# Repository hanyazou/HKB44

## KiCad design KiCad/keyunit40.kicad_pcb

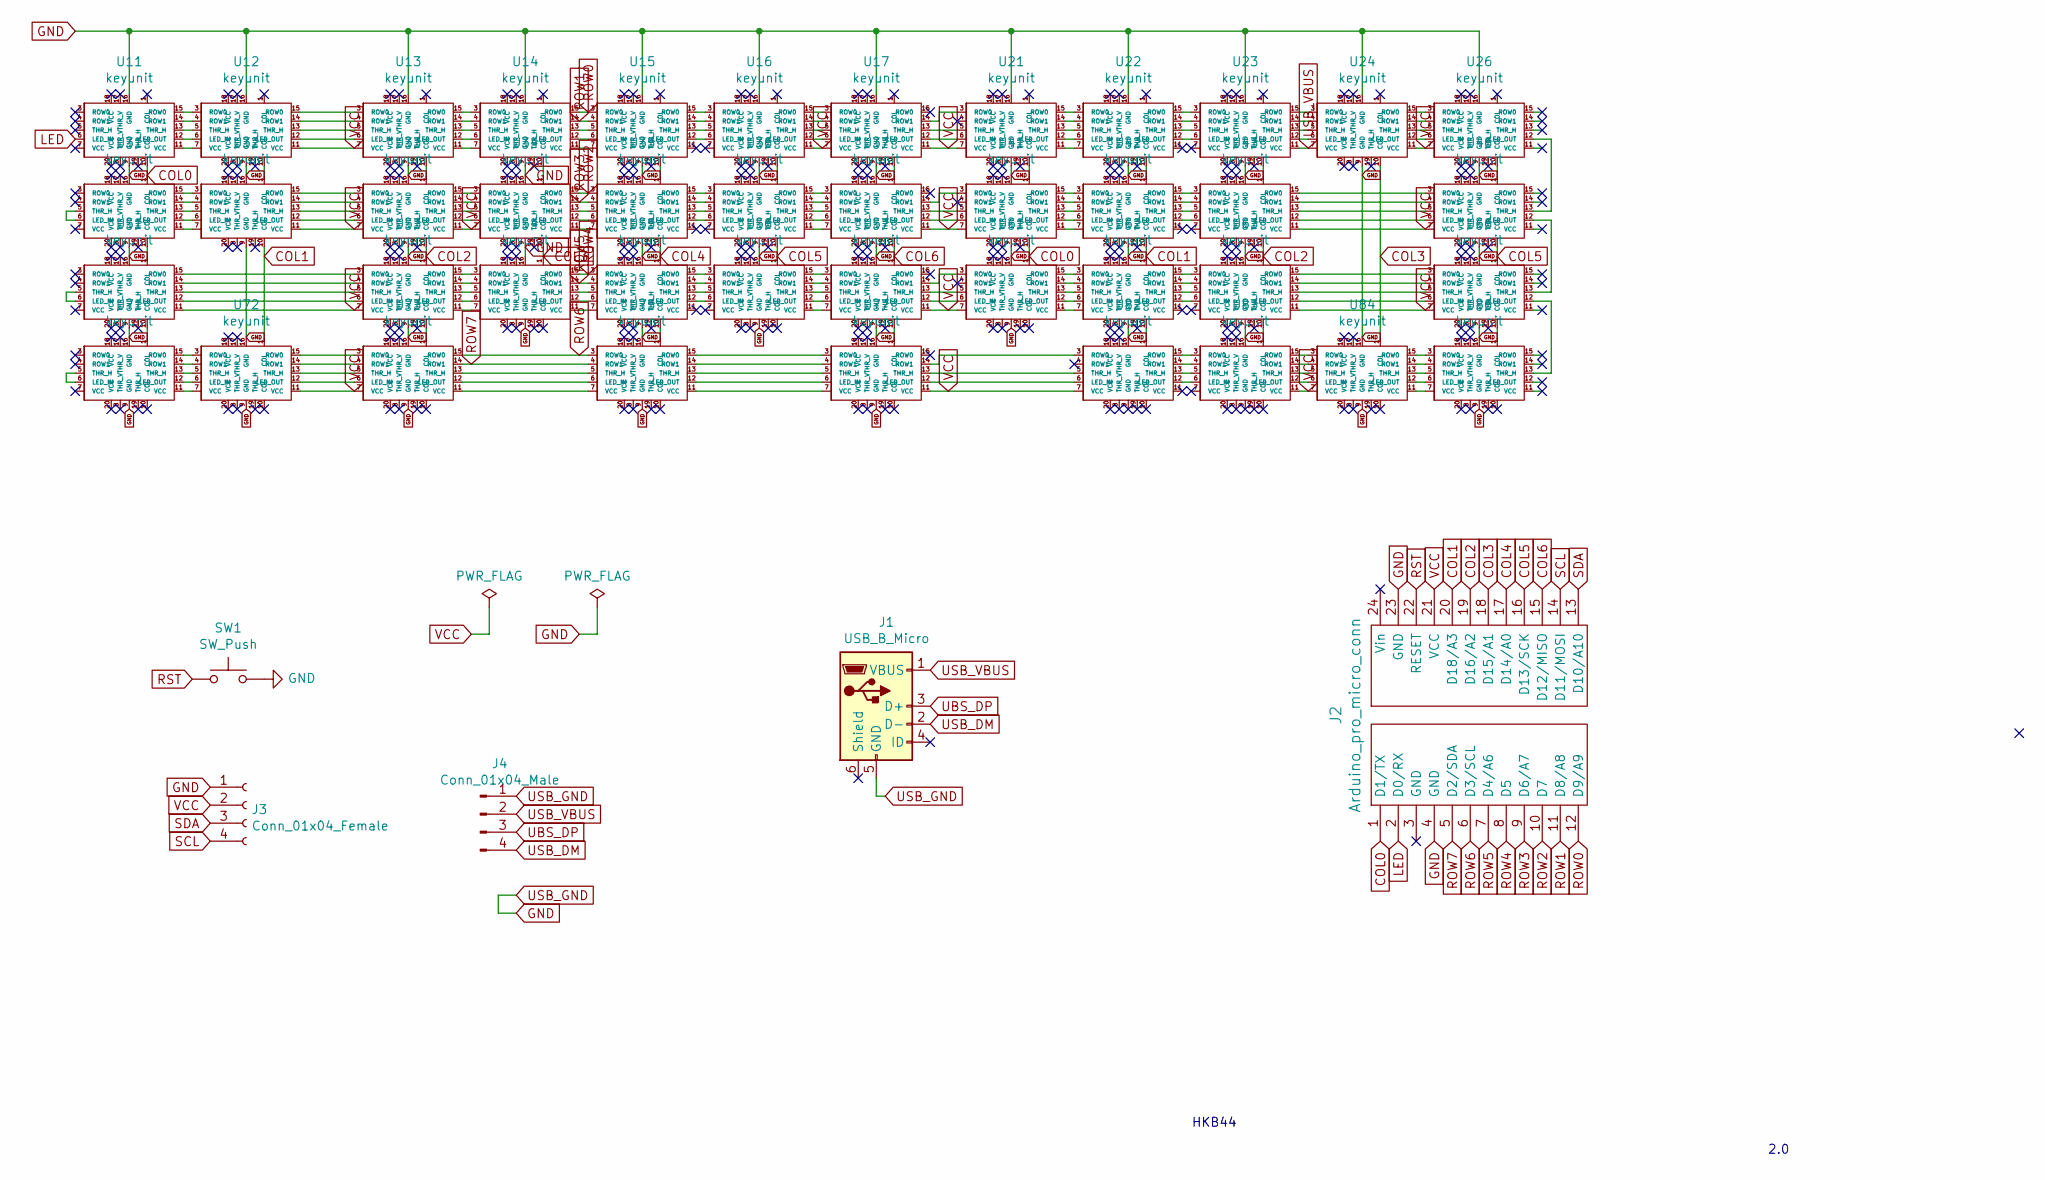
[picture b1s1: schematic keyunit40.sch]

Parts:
J1: USB_B_Micro; USB_Micro-B_Molex_47346-0001
J2: Arduino_pro_micro_conn; Arduino_pro_micro_0.85mm
J3: Conn_01x04_Female; JST_SH_BM04B-SRSS-TB_04x1.00mm_Straight
J4: Conn_01x04_Male; JST_SH_BM04B-SRSS-TB_04x1.00mm_Straight
SW1: SW_Push; push switch
U11, U12, U13, U14, U15, U16, U17, U21, U22, U23, U24, U26, U31, U32, U33, U34, U35, U36, U37, U41, U42, U43, U46, U51, U53, U54, U55, U56, U57, U61, U62, U63, U66, U71, U72, U73, U75, U77, U82, U83, U84, U86: keyunit

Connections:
COL0: J2.1 (D1/TX), U11.10 (COL), U31.1 (COL), U41.10 (COL), U61.1 (COL)
COL1: J2.20 (D18/A3), U32.10 (COL), U42.10 (COL), U62.1 (COL), U72.1 (COL)
COL2: J2.19 (D16/A2), U33.10 (COL), U43.10 (COL), U53.1 (COL), U63.1 (COL)
COL3: J2.18 (D15/A1), U24.10 (COL), U34.10 (COL), U54.1 (COL), U84.1 (COL)
COL4: J2.17 (D14/A0), U35.10 (COL), U55.1 (COL)
COL5: J2.16 (D13/SCK), U36.10 (COL), U46.10 (COL), U56.1 (COL), U66.1 (COL)
COL6: J2.15 (D12/MISO), U37.10 (COL), U57.1 (COL)
GND: J1.5 (GND), J2.4 (GND), J2.23 (GND), J3.1, J4.1, SW1.2, U11.9 (GND), U11.16 (GND), U12.9 (GND), U12.16 (GND), U13.9 (GND), U13.16 (GND), U14.9 (GND), U14.16 (GND), U15.9 (GND), U15.16 (GND), U16.9 (GND), U16.16 (GND), U17.9 (GND), U17.16 (GND), U21.9 (GND), U21.16 (GND), U22.9 (GND), U22.16 (GND), U23.9 (GND), U23.16 (GND), U24.9 (GND), U24.16 (GND), U26.9 (GND), U26.16 (GND), U31.9 (GND), U31.16 (GND), U32.9 (GND), U32.16 (GND), U33.9 (GND), U33.16 (GND), U34.9 (GND), U34.16 (GND), U35.9 (GND), U35.16 (GND), U36.9 (GND), U36.16 (GND), U37.9 (GND), U37.16 (GND), U41.9 (GND), U41.16 (GND), U42.9 (GND), U42.16 (GND), U43.9 (GND), U43.16 (GND), U46.9 (GND), U46.16 (GND), U51.9 (GND), U51.16 (GND), U53.9 (GND), U53.16 (GND), U54.9 (GND), U54.16 (GND), U55.9 (GND), U55.16 (GND), U56.9 (GND), U56.16 (GND), U57.9 (GND), U57.16 (GND), U61.9 (GND), U61.16 (GND), U62.9 (GND), U62.16 (GND), U63.9 (GND), U63.16 (GND), U66.9 (GND), U66.16 (GND), U71.9 (GND), U71.16 (GND), U72.9 (GND), U72.16 (GND), U73.9 (GND), U73.16 (GND), U75.9 (GND), U75.16 (GND), U77.9 (GND), U77.16 (GND), U82.16 (GND), U83.16 (GND), U84.9 (GND), U84.16 (GND), U86.9 (GND), U86.16 (GND)
LED: J2.2 (D0/RX), U11.6 (LED_IN)
unnamed: U11.11 (VCC), U12.7 (VCC)
unnamed: U11.12 (LED_OUT), U12.6 (LED_IN)
unnamed: U11.13 (THR_H), U12.5 (THR_H)
unnamed: U11.14 (ROW1), U12.4 (ROW1)
unnamed: U11.15 (ROW0), U12.3 (ROW0)
unnamed: U12.10 (COL), U32.1 (COL)
unnamed: U12.12 (LED_OUT), U13.6 (LED_IN)
unnamed: U12.13 (THR_H), U13.5 (THR_H)
unnamed: U12.14 (ROW1), U13.4 (ROW1)
unnamed: U12.15 (ROW0), U13.3 (ROW0)
unnamed: U13.10 (COL), U33.1 (COL)
unnamed: U13.11 (VCC), U14.7 (VCC)
unnamed: U13.12 (LED_OUT), U14.6 (LED_IN)
unnamed: U13.13 (THR_H), U14.5 (THR_H)
unnamed: U13.14 (ROW1), U14.4 (ROW1)
unnamed: U13.15 (ROW0), U14.3 (ROW0)
unnamed: U14.10 (COL), U34.1 (COL)
unnamed: U14.11 (VCC), U15.7 (VCC)
unnamed: U14.12 (LED_OUT), U15.6 (LED_IN)
unnamed: U14.13 (THR_H), U15.5 (THR_H)
unnamed: U15.10 (COL), U35.1 (COL)
unnamed: U15.12 (LED_OUT), U16.6 (LED_IN)
unnamed: U15.13 (THR_H), U16.5 (THR_H)
unnamed: U15.14 (ROW1), U16.4 (ROW1)
unnamed: U15.15 (ROW0), U16.3 (ROW0)
unnamed: U16.10 (COL), U36.1 (COL)
unnamed: U16.12 (LED_OUT), U17.6 (LED_IN)
unnamed: U16.13 (THR_H), U17.5 (THR_H)
unnamed: U16.14 (ROW1), U17.4 (ROW1)
unnamed: U16.15 (ROW0), U17.3 (ROW0)
unnamed: U17.10 (COL), U37.1 (COL)
unnamed: U17.12 (LED_OUT), U21.6 (LED_IN)
unnamed: U17.13 (THR_H), U21.5 (THR_H)
unnamed: U17.14 (ROW1), U21.3 (ROW0)
unnamed: U21.10 (COL), U41.1 (COL)
unnamed: U21.11 (VCC), U22.7 (VCC)
unnamed: U21.12 (LED_OUT), U22.6 (LED_IN)
unnamed: U21.13 (THR_H), U22.5 (THR_H)
unnamed: U21.14 (ROW1), U22.4 (ROW1)
unnamed: U21.15 (ROW0), U22.3 (ROW0)
unnamed: U22.10 (COL), U42.1 (COL)
unnamed: U22.12 (LED_OUT), U23.6 (LED_IN)
unnamed: U22.13 (THR_H), U23.5 (THR_H)
unnamed: U22.14 (ROW1), U23.4 (ROW1)
unnamed: U22.15 (ROW0), U23.3 (ROW0)
unnamed: U23.10 (COL), U43.1 (COL)
unnamed: U23.12 (LED_OUT), U24.6 (LED_IN)
unnamed: U23.13 (THR_H), U24.5 (THR_H)
unnamed: U23.14 (ROW1), U24.4 (ROW1)
unnamed: U23.15 (ROW0), U24.3 (ROW0)
unnamed: U24.12 (LED_OUT), U26.6 (LED_IN)
unnamed: U24.13 (THR_H), U26.5 (THR_H)
unnamed: U24.14 (ROW1), U26.4 (ROW1)
unnamed: U24.15 (ROW0), U26.3 (ROW0)
unnamed: U26.10 (COL), U46.1 (COL)
unnamed: U26.12 (LED_OUT), U46.13 (THR_H)
unnamed: U31.5 (THR_H), U31.6 (LED_IN)
unnamed: U31.10 (COL), U51.1 (COL)
unnamed: U31.11 (VCC), U32.7 (VCC)
unnamed: U31.12 (LED_OUT), U32.6 (LED_IN)
unnamed: U31.13 (THR_H), U32.5 (THR_H)
unnamed: U31.14 (ROW1), U32.4 (ROW1)
unnamed: U31.15 (ROW0), U32.3 (ROW0)
unnamed: U32.12 (LED_OUT), U33.6 (LED_IN)
unnamed: U32.13 (THR_H), U33.5 (THR_H)
unnamed: U32.14 (ROW1), U33.4 (ROW1)
unnamed: U32.15 (ROW0), U33.3 (ROW0)
unnamed: U33.12 (LED_OUT), U34.6 (LED_IN)
unnamed: U33.13 (THR_H), U34.5 (THR_H)
unnamed: U33.14 (ROW1), U34.4 (ROW1)
unnamed: U33.15 (ROW0), U34.3 (ROW0)
unnamed: U34.11 (VCC), U35.7 (VCC)
unnamed: U34.12 (LED_OUT), U35.6 (LED_IN)
unnamed: U34.13 (THR_H), U35.5 (THR_H)
unnamed: U35.12 (LED_OUT), U36.6 (LED_IN)
unnamed: U35.13 (THR_H), U36.5 (THR_H)
unnamed: U35.14 (ROW1), U36.4 (ROW1)
unnamed: U35.15 (ROW0), U36.3 (ROW0)
unnamed: U36.11 (VCC), U37.7 (VCC)
unnamed: U36.12 (LED_OUT), U37.6 (LED_IN)
unnamed: U36.13 (THR_H), U37.5 (THR_H)
unnamed: U36.14 (ROW1), U37.4 (ROW1)
unnamed: U36.15 (ROW0), U37.3 (ROW0)
unnamed: U37.12 (LED_OUT), U41.6 (LED_IN)
unnamed: U37.13 (THR_H), U41.5 (THR_H)
unnamed: U37.14 (ROW1), U41.3 (ROW0)
unnamed: U41.11 (VCC), U42.7 (VCC)
unnamed: U41.12 (LED_OUT), U42.6 (LED_IN)
unnamed: U41.13 (THR_H), U42.5 (THR_H)
unnamed: U41.14 (ROW1), U42.4 (ROW1)
unnamed: U41.15 (ROW0), U42.3 (ROW0)
unnamed: U42.12 (LED_OUT), U43.6 (LED_IN)
unnamed: U42.13 (THR_H), U43.5 (THR_H)
unnamed: U42.14 (ROW1), U43.4 (ROW1)
unnamed: U42.15 (ROW0), U43.3 (ROW0)
unnamed: U43.12 (LED_OUT), U46.6 (LED_IN)
unnamed: U43.13 (THR_H), U46.5 (THR_H)
unnamed: U43.14 (ROW1), U46.4 (ROW1)
unnamed: U43.15 (ROW0), U46.3 (ROW0)
unnamed: U46.12 (LED_OUT), U66.13 (THR_H)
unnamed: U51.5 (THR_H), U51.6 (LED_IN)
unnamed: U51.10 (COL), U71.1 (COL)
unnamed: U51.12 (LED_OUT), U53.6 (LED_IN)
unnamed: U51.13 (THR_H), U53.5 (THR_H)
unnamed: U51.14 (ROW1), U53.4 (ROW1)
unnamed: U51.15 (ROW0), U53.3 (ROW0)
unnamed: U53.10 (COL), U73.1 (COL)
unnamed: U53.11 (VCC), U54.7 (VCC)
unnamed: U53.12 (LED_OUT), U54.6 (LED_IN)
unnamed: U53.13 (THR_H), U54.5 (THR_H)
unnamed: U53.14 (ROW1), U54.4 (ROW1)
unnamed: U53.15 (ROW0), U54.3 (ROW0)
unnamed: U54.11 (VCC), U55.7 (VCC)
unnamed: U54.12 (LED_OUT), U55.6 (LED_IN)
unnamed: U54.13 (THR_H), U55.5 (THR_H)
unnamed: U55.10 (COL), U75.1 (COL)
unnamed: U55.12 (LED_OUT), U56.6 (LED_IN)
unnamed: U55.13 (THR_H), U56.5 (THR_H)
unnamed: U55.14 (ROW1), U56.4 (ROW1)
unnamed: U55.15 (ROW0), U56.3 (ROW0)
unnamed: U56.11 (VCC), U57.7 (VCC)
unnamed: U56.12 (LED_OUT), U57.6 (LED_IN)
unnamed: U56.13 (THR_H), U57.5 (THR_H)
unnamed: U56.14 (ROW1), U57.4 (ROW1)
unnamed: U56.15 (ROW0), U57.3 (ROW0)
unnamed: U57.10 (COL), U77.1 (COL)
unnamed: U57.12 (LED_OUT), U61.6 (LED_IN)
unnamed: U57.13 (THR_H), U61.5 (THR_H)
unnamed: U57.14 (ROW1), U61.3 (ROW0)
unnamed: U61.11 (VCC), U62.7 (VCC)
unnamed: U61.12 (LED_OUT), U62.6 (LED_IN)
unnamed: U61.13 (THR_H), U62.5 (THR_H)
unnamed: U61.14 (ROW1), U62.4 (ROW1)
unnamed: U61.15 (ROW0), U62.3 (ROW0)
unnamed: U62.10 (COL), U82.1 (COL)
unnamed: U62.12 (LED_OUT), U63.6 (LED_IN)
unnamed: U62.13 (THR_H), U63.5 (THR_H)
unnamed: U62.14 (ROW1), U63.4 (ROW1)
unnamed: U62.15 (ROW0), U63.3 (ROW0)
unnamed: U63.10 (COL), U83.1 (COL)
unnamed: U63.12 (LED_OUT), U66.6 (LED_IN)
unnamed: U63.13 (THR_H), U66.5 (THR_H)
unnamed: U63.14 (ROW1), U66.4 (ROW1)
unnamed: U63.15 (ROW0), U66.3 (ROW0)
unnamed: U66.10 (COL), U86.1 (COL)
unnamed: U66.12 (LED_OUT), U86.13 (THR_H)
unnamed: U71.5 (THR_H), U71.6 (LED_IN)
unnamed: U71.11 (VCC), U72.7 (VCC)
unnamed: U71.12 (LED_OUT), U72.6 (LED_IN)
unnamed: U71.13 (THR_H), U72.5 (THR_H)
unnamed: U71.14 (ROW1), U72.4 (ROW1)
unnamed: U71.15 (ROW0), U72.3 (ROW0)
unnamed: U72.12 (LED_OUT), U73.6 (LED_IN)
unnamed: U72.13 (THR_H), U73.5 (THR_H)
unnamed: U72.14 (ROW1), U73.4 (ROW1)
unnamed: U72.15 (ROW0), U73.3 (ROW0)
unnamed: U73.11 (VCC), U75.7 (VCC)
unnamed: U73.12 (LED_OUT), U75.6 (LED_IN)
unnamed: U73.13 (THR_H), U75.5 (THR_H)
unnamed: U75.11 (VCC), U77.7 (VCC)
unnamed: U75.12 (LED_OUT), U77.6 (LED_IN)
unnamed: U75.13 (THR_H), U77.5 (THR_H)
unnamed: U75.14 (ROW1), U77.4 (ROW1)
unnamed: U75.15 (ROW0), U77.3 (ROW0)
unnamed: U77.12 (LED_OUT), U82.6 (LED_IN)
unnamed: U77.13 (THR_H), U82.5 (THR_H)
unnamed: U77.14 (ROW1), U82.3 (ROW0)
unnamed: U82.12 (LED_OUT), U83.6 (LED_IN)
unnamed: U82.13 (THR_H), U83.5 (THR_H)
unnamed: U82.14 (ROW1), U83.4 (ROW1)
unnamed: U82.15 (ROW0), U83.3 (ROW0)
unnamed: U83.12 (LED_OUT), U84.6 (LED_IN)
unnamed: U83.13 (THR_H), U84.5 (THR_H)
unnamed: U83.14 (ROW1), U84.4 (ROW1)
unnamed: U83.15 (ROW0), U84.3 (ROW0)
unnamed: U84.11 (VCC), U86.7 (VCC)
unnamed: U84.12 (LED_OUT), U86.6 (LED_IN)
unnamed: U84.13 (THR_H), U86.5 (THR_H)
unnamed: U84.14 (ROW1), U86.4 (ROW1)
unnamed: U84.15 (ROW0), U86.3 (ROW0)
ROW0: J2.12 (D9/A9), U14.15 (ROW0), U15.3 (ROW0)
ROW1: J2.11 (D8/A8), U14.14 (ROW1), U15.4 (ROW1)
ROW2: J2.10 (D7), U34.15 (ROW0), U35.3 (ROW0)
ROW3: J2.9 (D6/A7), U34.14 (ROW1), U35.4 (ROW1)
ROW4: J2.8 (D5), U54.15 (ROW0), U55.3 (ROW0)
ROW5: J2.7 (D4/A6), U54.14 (ROW1), U55.4 (ROW1)
ROW6: J2.6 (D3/SCL), U73.15 (ROW0), U75.3 (ROW0)
ROW7: J2.5 (D2/SDA), U73.14 (ROW1), U75.4 (ROW1)
RST: J2.22 (RESET), SW1.1
SCL: J2.14 (D11/MOSI), J3.4
SDA: J2.13 (D10/A10), J3.3
UBS_DP: J1.3 (D+), J4.3
USB_DM: J1.2 (D-), J4.4
USB_VBUS: J1.1 (VBUS), J4.2, U23.11 (VCC), U24.7 (VCC)
VCC: J2.21 (VCC), J3.2, U12.11 (VCC), U13.7 (VCC), U16.11 (VCC), U17.7 (VCC), U17.11 (VCC), U21.7 (VCC), U24.11 (VCC), U26.7 (VCC), U32.11 (VCC), U33.7 (VCC), U33.11 (VCC), U34.7 (VCC), U37.11 (VCC), U41.7 (VCC), U43.11 (VCC), U46.7 (VCC), U51.11 (VCC), U53.7 (VCC), U57.11 (VCC), U61.7 (VCC), U63.11 (VCC), U66.7 (VCC), U72.11 (VCC), U73.7 (VCC), U77.11 (VCC), U82.7 (VCC), U83.11 (VCC), U84.7 (VCC)

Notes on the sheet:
HKB44
2.0

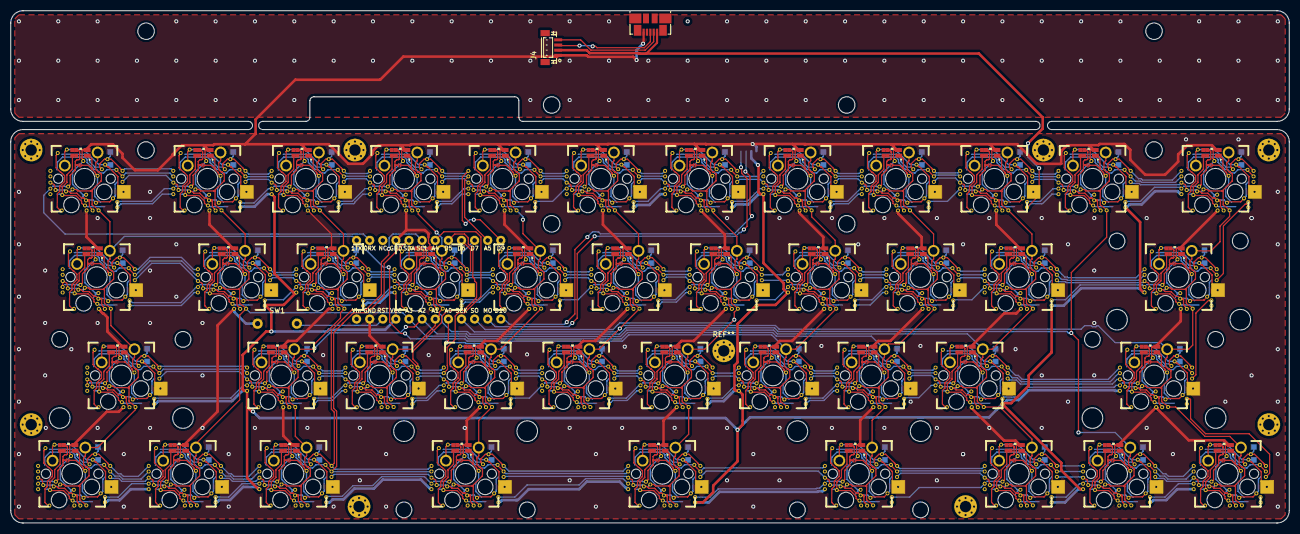
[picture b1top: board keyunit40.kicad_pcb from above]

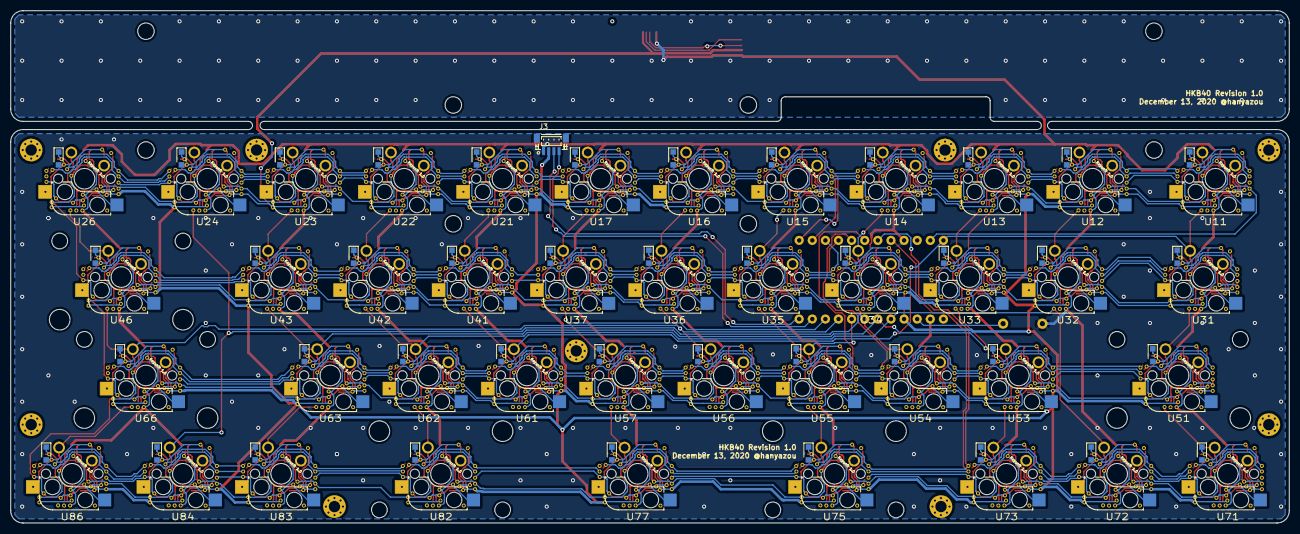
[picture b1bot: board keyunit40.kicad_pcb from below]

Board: 2 copper layers, 247.7 x 99.2 mm, 52 parts (2 on the bottom side), 204 nets.

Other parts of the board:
225u, 225u#2, 225u#3, 225u#4: Stabilizer; MX_STABI_225H
275u: Stabilizer; MX_STABI_275H

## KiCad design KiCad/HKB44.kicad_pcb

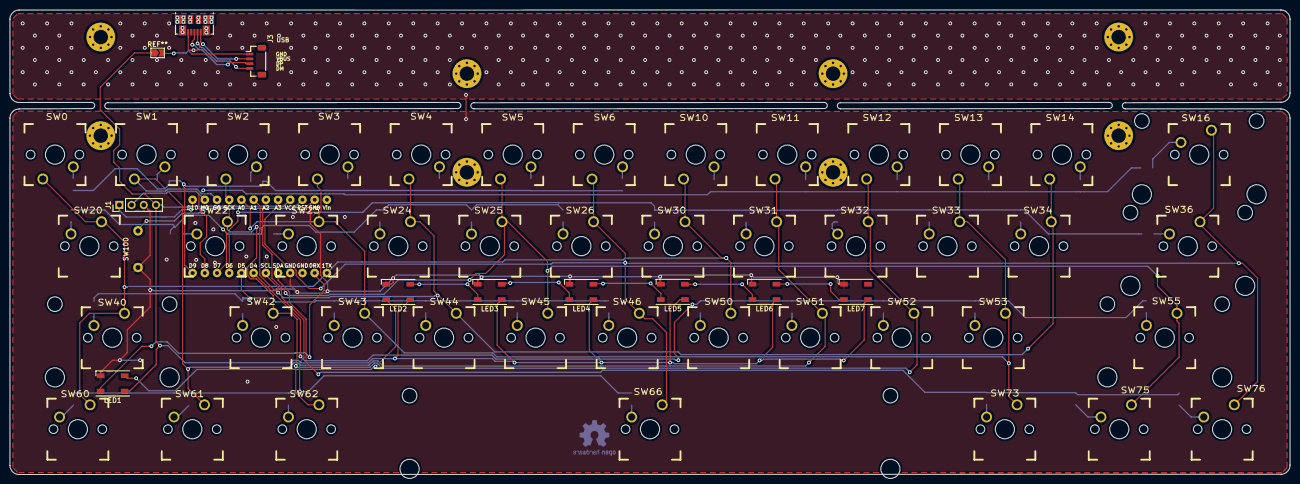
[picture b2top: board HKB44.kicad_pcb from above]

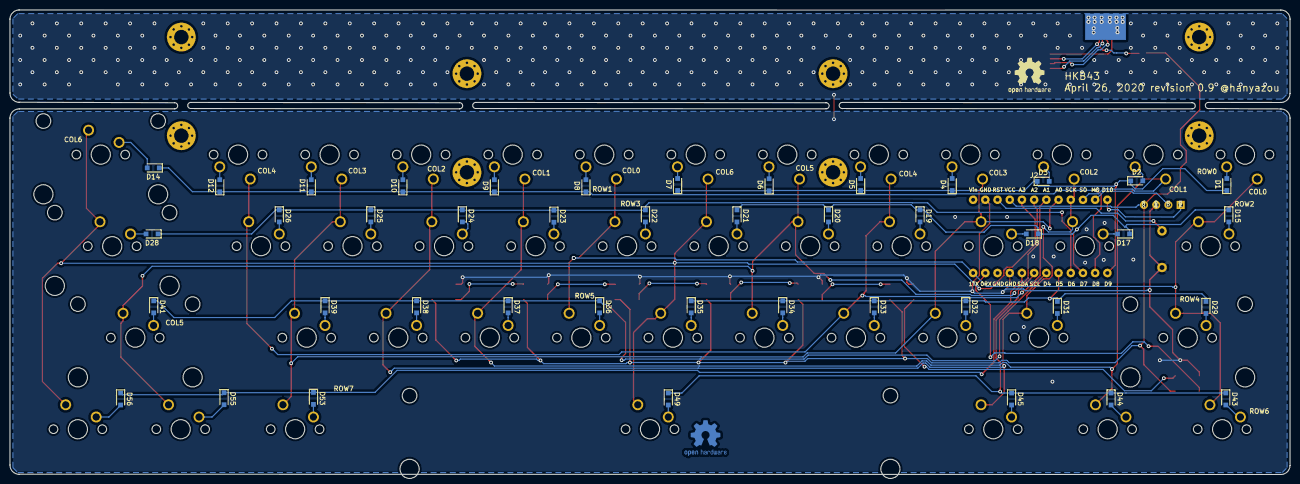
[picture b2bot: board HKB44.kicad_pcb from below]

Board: 2 copper layers, 266.4 x 96.7 mm, 98 parts (44 on the bottom side), 74 nets.

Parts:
D1, D2, D3, D4, D5, D6, D7, D8, D9, D10, D11, D12, D14, D15, D17, D18, D19, D20, D21, D22, D23, D24, D25, D26, D28, D29, D31, D32, D33, D34, D35, D36, D37, D38, D39, D41, D43, D44, D45, D49, D53, D55, D56: 1N4148; D_SOD-323_HandSoldering
J1: Conn_01x04_Female; PinHeader_1x04_P2.54mm_Vertical
J2: Arduino_pro_micro_conn
J3: Conn_01x04_Male; JST_SH_BM04B-SRSS-TB_1x04-1MP_P1.00mm_Vertical
J4: USB_B_Micro; USB_Micro-B_Molex_47346-0001
LED1, LED2, LED3, LED4, LED5, LED6, LED7: WS2812B; LED_WS2812B-PLCC4
SW0, SW1, SW2, SW3, SW4, SW5, SW6, SW10, SW11, SW12, SW13, SW14, SW22, SW23, SW24, SW25, SW26, SW30, SW31, SW32, SW33, SW34, SW42, SW43, SW44, SW45, SW46, SW50, SW51, SW52, SW53, SW75: SW_Push; MX_PCB_100H
SW16: SW_Push; MX_PCB_200H
SW20: SW_Push; MX_PCB_175H
SW36, SW40: SW_Push; MX_PCB_225H
SW55: SW_Push; MX_PCB_275H
SW60, SW61, SW62, SW76: SW_Push; MX_PCB_125H
SW66: SW_Push; MX_PCB_625H
SW73: SW_Push; MX_PCB_150H
SW100: SW_Push; push switch

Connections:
COL0: J2.1, SW0.1, SW10.1, SW20.1, SW30.1, SW40.1, SW50.1, SW60.1
COL1: J2.15, SW1.1, SW11.1, SW31.1, SW51.1, SW61.1
COL2: J2.16, SW2.1, SW12.1, SW22.1, SW32.1, SW42.1, SW52.1, SW62.1
COL3: J2.17, SW3.1, SW13.1, SW23.1, SW33.1, SW43.1, SW53.1, SW73.1
COL4: J2.18, SW4.1, SW14.1, SW24.1, SW34.1, SW44.1
COL5: J2.19, SW5.1, SW25.1, SW45.1, SW55.1, SW75.1
COL6: J2.20, SW6.1, SW16.1, SW26.1, SW36.1, SW46.1, SW66.1, SW76.1
GND: J1.3, J2.4, J2.23, LED1.3, LED2.3, LED3.3, LED4.3, LED5.3, LED6.3, LED7.3, SW100.2
LED: J2.2, LED1.4
unnamed: D1.2, SW0.2
unnamed: D2.2, SW1.2
unnamed: D3.2, SW2.2
unnamed: D4.2, SW3.2
unnamed: D5.2, SW4.2
unnamed: D6.2, SW5.2
unnamed: D7.2, SW6.2
unnamed: D8.2, SW10.2
unnamed: D9.2, SW11.2
unnamed: D10.2, SW12.2
unnamed: D11.2, SW13.2
unnamed: D12.2, SW14.2
unnamed: D14.2, SW16.2
unnamed: D15.2, SW20.2
unnamed: D17.2, SW22.2
unnamed: D18.2, SW23.2
unnamed: D19.2, SW24.2
unnamed: D20.2, SW25.2
unnamed: D21.2, SW26.2
unnamed: D22.2, SW30.2
unnamed: D23.2, SW31.2
unnamed: D24.2, SW32.2
unnamed: D25.2, SW33.2
unnamed: D26.2, SW34.2
unnamed: D28.2, SW36.2
unnamed: D29.2, SW40.2
unnamed: D31.2, SW42.2
unnamed: D32.2, SW43.2
unnamed: D33.2, SW44.2
unnamed: D34.2, SW45.2
unnamed: D35.2, SW46.2
unnamed: D36.2, SW50.2
unnamed: D37.2, SW51.2
unnamed: D38.2, SW52.2
unnamed: D39.2, SW53.2
unnamed: D41.2, SW55.2
unnamed: D43.2, SW60.2
unnamed: D44.2, SW61.2
unnamed: D45.2, SW62.2
unnamed: D49.2, SW66.2
unnamed: D53.2, SW73.2
unnamed: D55.2, SW75.2
unnamed: D56.2, SW76.2
unnamed: LED1.2, LED2.4
unnamed: LED2.2, LED3.4
unnamed: LED3.2, LED4.4
unnamed: LED4.2, LED5.4
unnamed: LED5.2, LED6.4
unnamed: LED6.2, LED7.4
ROW0: D1.1, D2.1, D3.1, D4.1, D5.1, D6.1, D7.1, J2.12
ROW1: D8.1, D9.1, D10.1, D11.1, D12.1, D14.1, J2.11
ROW2: D15.1, D17.1, D18.1, D19.1, D20.1, D21.1, J2.10
ROW3: D22.1, D23.1, D24.1, D25.1, D26.1, D28.1, J2.9
ROW4: D29.1, D31.1, D32.1, D33.1, D34.1, D35.1, J2.8
ROW5: D36.1, D37.1, D38.1, D39.1, D41.1, J2.7
ROW6: D43.1, D44.1, D45.1, D49.1, J2.6
ROW7: D53.1, D55.1, D56.1, J2.5
RST: J2.22, SW100.1
SCL: J1.2, J2.14
SDA: J1.1, J2.13
UBS_DP: J3.3, J4.3
USB_DM: J3.4, J4.2
USB_GND: J3.1, J4.5
USB_VBUS: J3.2, J4.1
VCC: J1.4, J2.21, LED1.1, LED2.1, LED3.1, LED4.1, LED5.1, LED6.1, LED7.1

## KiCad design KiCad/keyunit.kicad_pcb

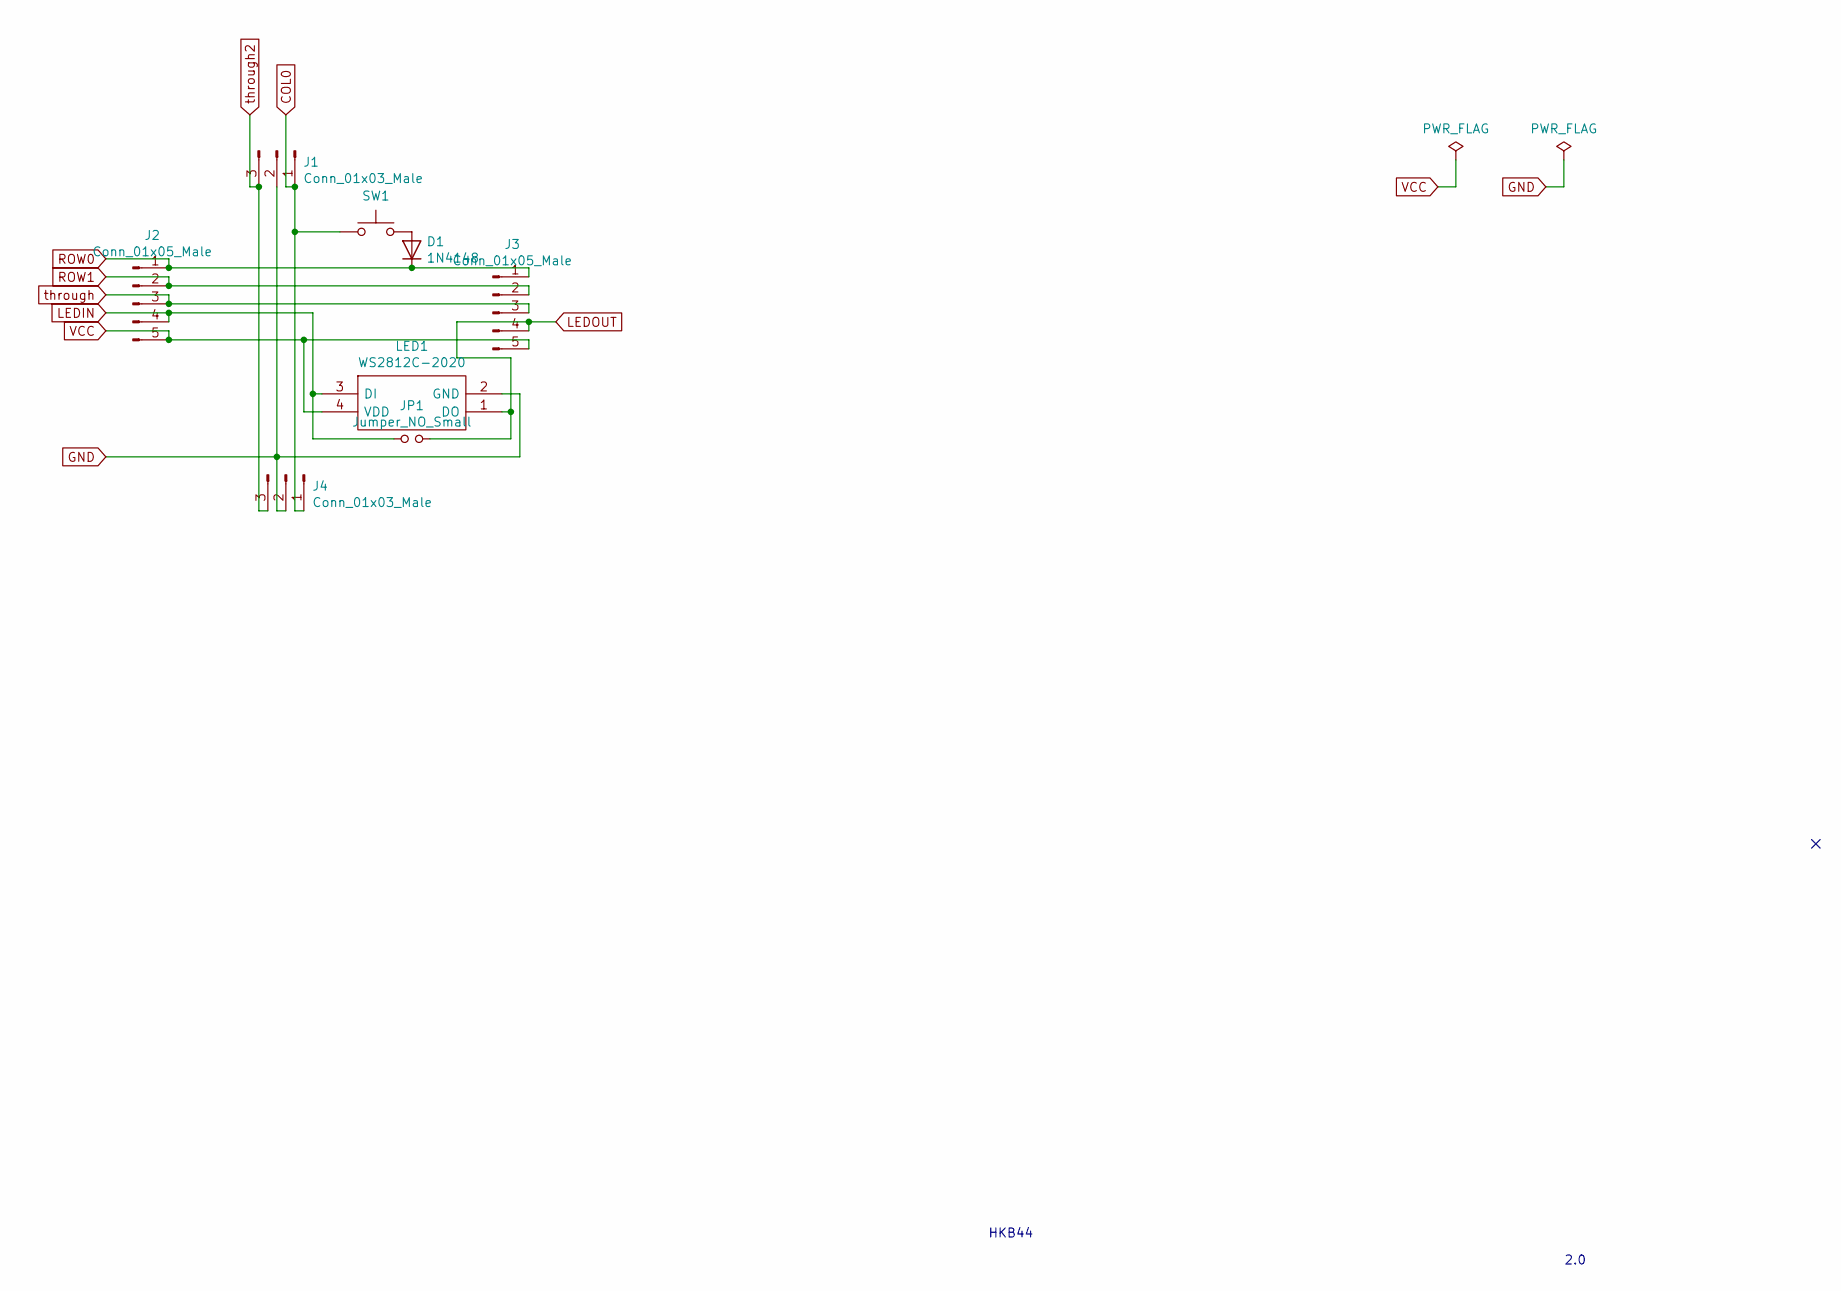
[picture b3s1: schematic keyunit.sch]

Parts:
D1: 1N4148; D_SOD-323_HandSoldering
J1, J4: Conn_01x03_Male; PinHeader_1x03_P2.54mm_Vertical
J2, J3: Conn_01x05_Male; PinHeader_1x05_P2.54mm_Vertical
JP1: Jumper_NO_Small; SolderJumper-2_small
LED1: WS2812C-2020; WS2812C2020; Manufacturer_Part_Number WS2812C-2020
SW1: SW_Push; MX_PCB_100H_socket

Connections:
COL0: J1.1, J4.1, SW1.1
GND: J1.2, J4.2, LED1.2 (GND)
LEDIN: J2.4, JP1.1, LED1.3 (DI)
LEDOUT: J3.4, JP1.2, LED1.1 (DO)
unnamed: D1.2 (A), SW1.2
ROW0: D1.1 (K), J2.1, J3.1
ROW1: J2.2, J3.2
VCC: J2.5, J3.5, LED1.4 (VDD)
through: J2.3, J3.3
through2: J1.3, J4.3

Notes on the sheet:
HKB44
2.0

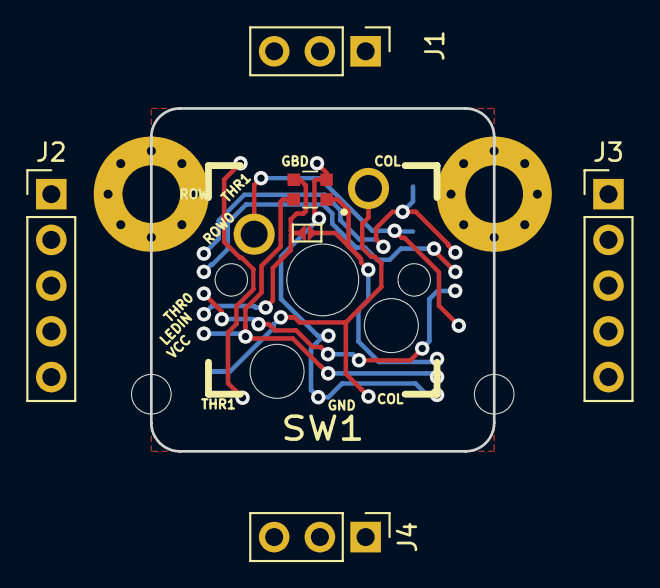
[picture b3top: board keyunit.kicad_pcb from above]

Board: 2 copper layers, 19.1 x 19.1 mm, 8 parts (1 on the bottom side), 10 nets.

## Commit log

2020-04-25 HKB45 initial version 0.5
2020-04-26 HKB43 version 0.9
2020-05-04 Add Kailh socket foorprints
2020-05-04 Fix keymap for 43 keys
2020-05-31 keyunit x4 key board for POC
2020-05-31 Add copy of hkb44 as keyunit4
2020-05-31 Fix KeyUnit4 QMK firmware
2020-05-31 Add MX_PLATE_100H.kicad_mod
2020-06-13 Add keyunit2 firmware (copy of keyunit4)
2020-06-14 Add keyunit foot print and keyunit2 board
2020-06-14 Fix keyunit2 firmware
2020-06-14 Revert HKB44 board changes
2020-06-14 Add cherry mx plat footprint and fix HKB44 plate board
2020-11-09 HKB44 keyunit version 0.9
2020-11-09 Output gerber and add .zip files
2020-11-21 Fixed
2020-11-23 Fix QMK firmware for HKB44 keyunit version 0.9
2020-11-28 Fix keyunit44 version 1.0
2020-12-12 Use all 44 LEDs
2020-12-27 HKB40 Rev 1.0
2021-04-03 Add frame 3D CAD data
2021-04-03 Enlarge cable hole of frame
